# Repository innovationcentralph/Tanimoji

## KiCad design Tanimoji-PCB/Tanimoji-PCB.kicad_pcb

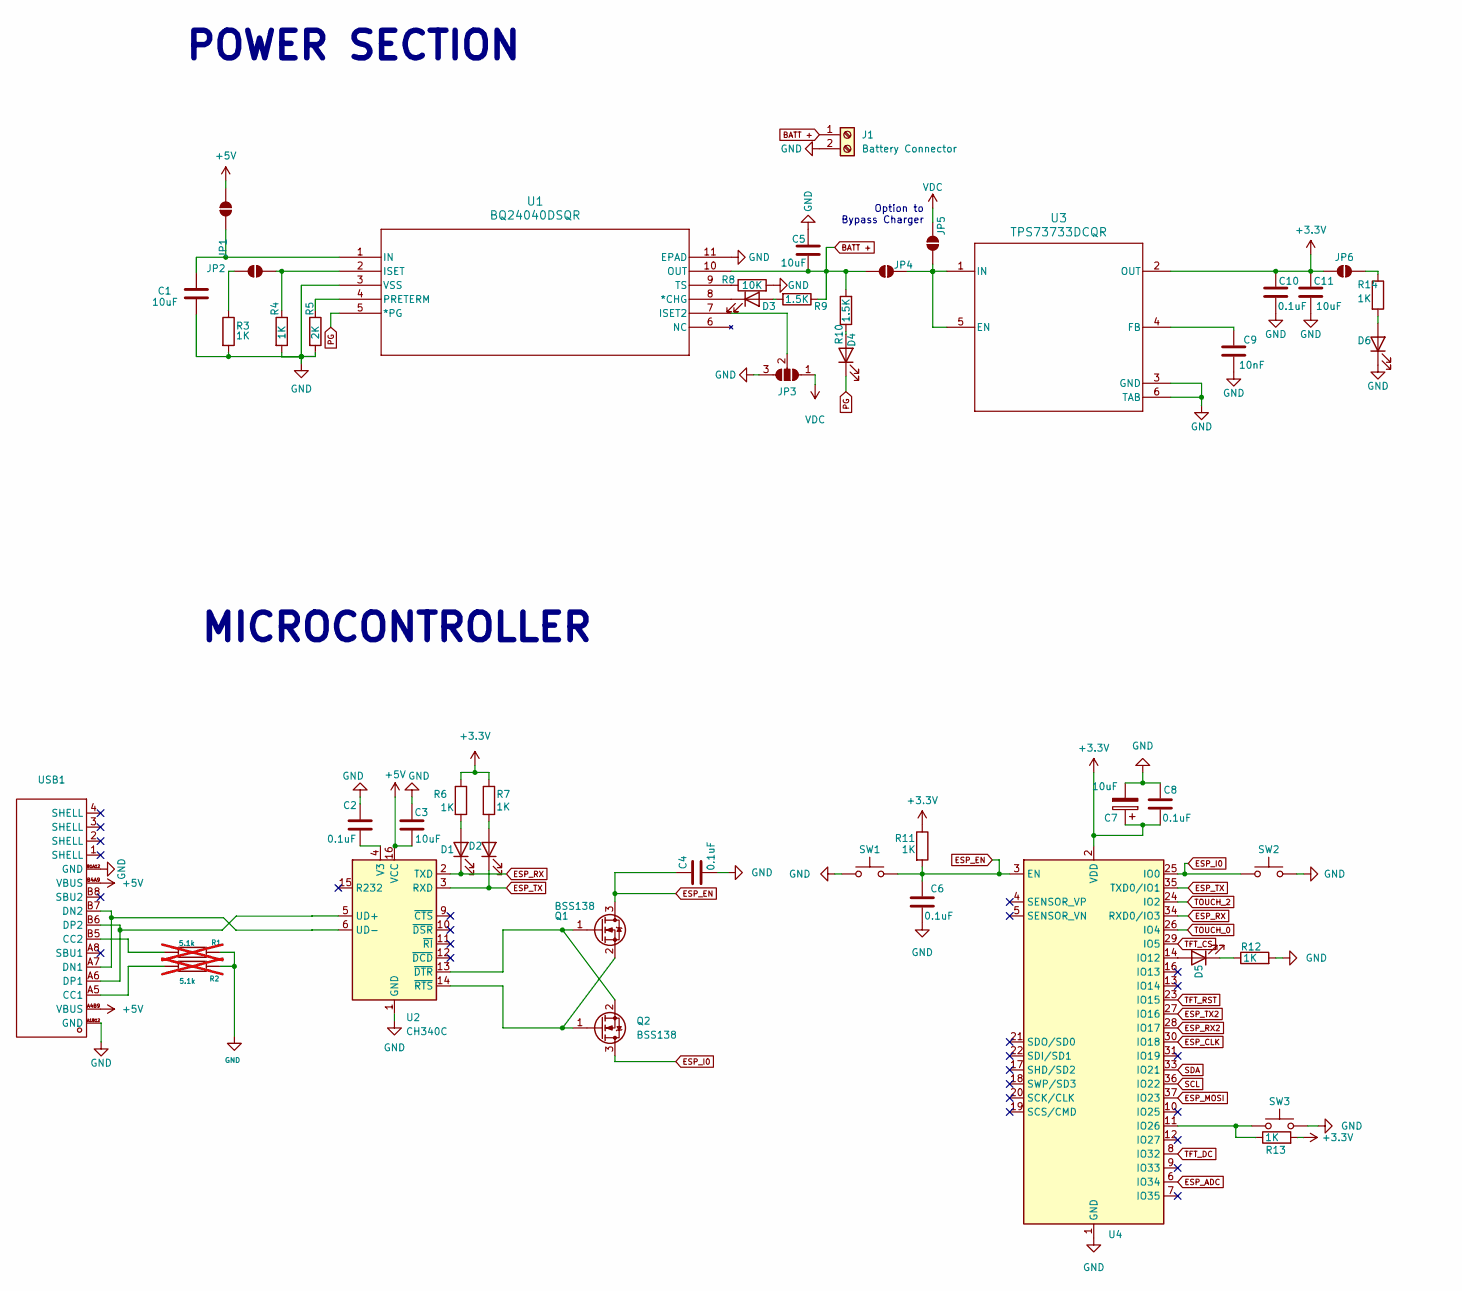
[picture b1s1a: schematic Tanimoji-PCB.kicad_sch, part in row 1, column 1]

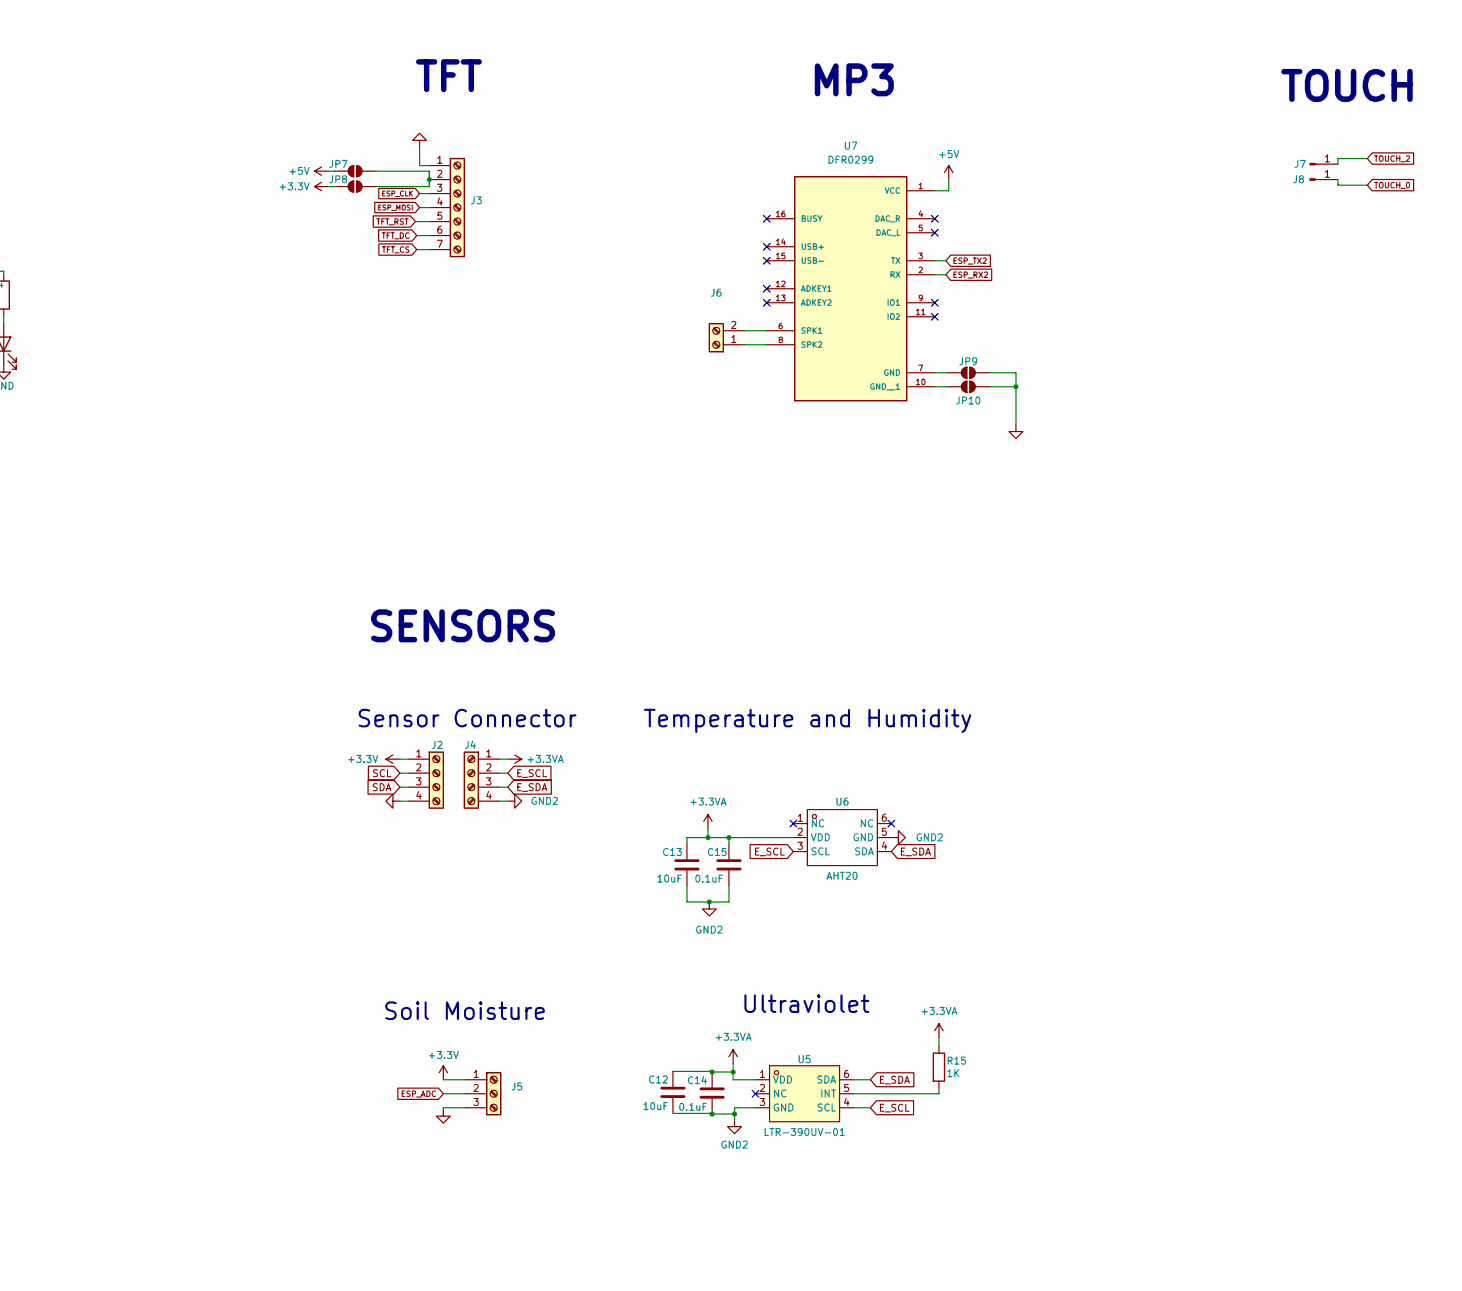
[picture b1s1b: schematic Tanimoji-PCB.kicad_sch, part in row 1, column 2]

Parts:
C1, C3, C5, C7, C11, C12, C13: 10uF; C_0805_2012Metric_Pad1.18x1.45mm_HandSolder; LCSC C15850
C2, C4, C6, C8, C10, C14, C15: 0.1uF; C_0805_2012Metric_Pad1.18x1.45mm_HandSolder; LCSC C49678
C9: 10nF; C_0402_1005Metric; LCSC C60133
D1, D2, D5, D6: LED; LED_0805_2012Metric_Pad1.15x1.40mm_HandSolder; LCSC C2297
D3: CHG; LED_0805_2012Metric_Pad1.15x1.40mm_HandSolder; LCSC C2286
D4: PGOOD; LED_0805_2012Metric_Pad1.15x1.40mm_HandSolder; LCSC C2297
J1: Battery Connector; JST_XH_B2B-XH-AM_1x02_P2.50mm_Vertical
J2, J4: Screw_Terminal_01x04; JST_XH_B4B-XH-AM_1x04_P2.50mm_Vertical
J3: Screw_Terminal_01x07; JST_XH_B7B-XH-AM_1x07_P2.50mm_Vertical
J5: Screw_Terminal_01x03; JST_XH_B3B-XH-AM_1x03_P2.50mm_Vertical
J6: Screw_Terminal_01x02; JST_XH_B2B-XH-AM_1x02_P2.50mm_Vertical
J7, J8: Conn_01x01_Pin; TestPoint_Loop_D2.54mm_Drill1.5mm_Beaded
JP1, JP2, JP4, JP5, JP6, JP7, JP8, JP9, JP10: SolderJumper_2_Open; SolderJumper-2_P1.3mm_Open_RoundedPad1.0x1.5mm
JP3: SolderJumper_3_Open; SolderJumper-3_P1.3mm_Open_RoundedPad1.0x1.5mm
Q1, Q2: BSS138; SOT-23; LCSC C426569
R1, R2: 5.1k; R_0603_1608Metric_Pad0.98x0.95mm_HandSolder; LCSC C103079; not fitted
R3, R4, R6, R7, R11, R12, R13, R14, R15: 1K; R_0603_1608Metric_Pad0.98x0.95mm_HandSolder; LCSC C21190
R5: 2K; R_0603_1608Metric_Pad0.98x0.95mm_HandSolder; LCSC C22975
R8: 10K; R_0603_1608Metric_Pad0.98x0.95mm_HandSolder; LCSC C25804
R9, R10: 1.5K; R_0603_1608Metric_Pad0.98x0.95mm_HandSolder; LCSC C22843
SW1, SW2: SW_Push; SW_Tactile_SPST_NO_Straight_CK_PTS636Sx25SMTRLFS; LCSC C2689642
SW3: SW_Push; SW_PUSH_6mm_H9.5mm; LCSC C2689642
U1: BQ24040DSQR; WSON-10_L2.0-W2.0-P0.40-BL-EP; LCSC C81080
U2: CH340C; SOP-16_3.9x9.9mm_P1.27mm; LCSC C84681
U3: TPS73733DCQR; SOT-223-6_L6.5-W3.5-P1.27-BL; LCSC C31334
U4: ESP32-WROOM-32; ESP32-WROOM-32U; LCSC C529577
U5: LTR-390UV-01; SENSOR-SMD_LTR-390UV-01; LCSC Part C492374
U6: AHT20; SENSOR-SMD_L3.0-W3.0-P1.00-BR; Manufacturer Part AHT20; LCSC Part Name AHT20
U7: DFR0299; MODULE_DFR0299
USB1: USB-C-SMD_TYPE-C16PIN; Manufacturer Part TYPE-C16PIN; LCSC Part Name Type-C 母 卧贴

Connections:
+3.3V: C7.1, C8.1, C10.2, C11.2, J2.1, J5.1, JP6.1 (A), JP8.1 (A), R6.1, R7.1, R11.1, R13.2, U3.2 (OUT), U4.2 (VDD)
+3.3VA: C12.1, C13.1, C14.2, C15.1, J4.1, R15.1, U5.1 (VDD), U6.2 (VDD)
+5V: C3.1, JP1.1 (A), JP7.1 (A), U2.16 (VCC), U7.1 (VCC), USB1.A4B9 (VBUS), USB1.B4A9 (VBUS)
BATT +: C5.2, J1.1, JP4.1 (A), R9.1, R10.2, U1.10 (OUT)
ESP_ADC: J5.2, U4.6 (IO34)
ESP_CLK: J3.3, U4.30 (IO18)
ESP_EN: C4.2, C6.2, Q1.3 (D), R11.2, SW1.2, U4.3 (EN)
ESP_I0: Q2.3 (D), SW2.1, U4.25 (IO0)
ESP_MOSI: J3.4, U4.37 (IO23)
ESP_RX: D1.1 (K), U2.2 (TXD), U4.34 (RXD0/IO3)
ESP_RX2: U4.28 (IO17), U7.2 (RX)
ESP_TX: D2.1 (K), U2.3 (RXD), U4.35 (TXD0/IO1)
ESP_TX2: U4.27 (IO16), U7.3 (TX)
E_SCL: J4.2, U5.4 (SCL), U6.3 (SCL)
E_SDA: J4.3, U5.6 (SDA), U6.4 (SDA)
GND: C1.2, C2.2, C3.2, C4.1, C5.1, C6.1, C7.2, C8.2, C9.1, C10.1, C11.1, D6.1 (K), J1.2, J2.4, J3.1, J5.3, JP3.3 (B), JP9.2 (B), JP10.2 (B), R1.2, R2.2, R3.2, R4.2, R5.2, R8.2, R12.2, SW1.1, SW2.2, SW3.2, U1.3 (VSS), U1.11 (EPAD), U2.1 (GND), U3.3 (GND), U3.6 (TAB), U4.1 (GND), U4.15 (GND), U4.38 (GND), U4.39 (GND), USB1.A1B12 (GND), USB1.B1A12 (GND)
GND2: C12.2, C13.2, C14.1, C15.2, J4.4, U5.3 (GND), U6.5 (GND)
unnamed: D1.2 (A), R6.2
unnamed: D2.2 (A), R7.2
unnamed: D3.2 (A), R9.2
unnamed: D3.1 (K), U1.8 (*CHG)
unnamed: D4.2 (A), R10.1
unnamed: D5.2 (A), U4.14 (IO12)
unnamed: D5.1 (K), R12.1
unnamed: D6.2 (A), R14.2
unnamed: J3.2, JP7.2 (B), JP8.2 (B)
unnamed: J6.1, U7.8 (SPK2)
unnamed: J6.2, U7.6 (SPK1)
unnamed: C1.1, JP1.2 (B), U1.1 (IN)
unnamed: JP2.1 (A), R4.1, U1.2 (ISET)
unnamed: JP2.2 (B), R3.1
unnamed: JP3.2 (C), U1.7 (ISET2)
unnamed: JP4.2 (B), JP5.2 (B), U3.1 (IN), U3.5 (EN)
unnamed: JP6.2 (B), R14.1
unnamed: JP9.1 (A), U7.7 (GND)
unnamed: JP10.1 (A), U7.10 (GND__1)
unnamed: Q1.1 (G), Q2.2 (S), U2.13 (~DTR)
unnamed: Q1.2 (S), Q2.1 (G), U2.14 (~RTS)
unnamed: R5.1, U1.4 (PRETERM)
unnamed: R8.1, U1.9 (TS)
unnamed: U2.5 (UD+), USB1.A6 (DP1), USB1.B6 (DP2)
unnamed: U2.6 (UD-), USB1.A7 (DN1), USB1.B7 (DN2)
unnamed: C2.1, U2.4 (V3)
unnamed: C9.2, U3.4 (FB)
unnamed: R13.1, SW3.1, U4.11 (IO26)
unnamed: R15.2, U5.5 (INT)
unnamed: R2.1, USB1.A5 (CC1)
unnamed: R1.1, USB1.B5 (CC2)
PG: D4.1 (K), U1.5 (*PG)
SCL: J2.2, U4.36 (IO22)
SDA: J2.3, U4.33 (IO21)
TFT_CS: J3.7, U4.29 (IO5)
TFT_DC: J3.6, U4.8 (IO32)
TFT_RST: J3.5, U4.23 (IO15)
TOUCH_0: J8.1, U4.26 (IO4)
TOUCH_2: J7.1, U4.24 (IO2)
VDC: JP3.1 (A), JP5.1 (A)

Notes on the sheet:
Temperature and Humidity
TOUCH
SENSORS
MICROCONTROLLER
MP3
Sensor Connector
Soil Moisture
TFT
POWER SECTION
Option to Bypass Charger
Ultraviolet

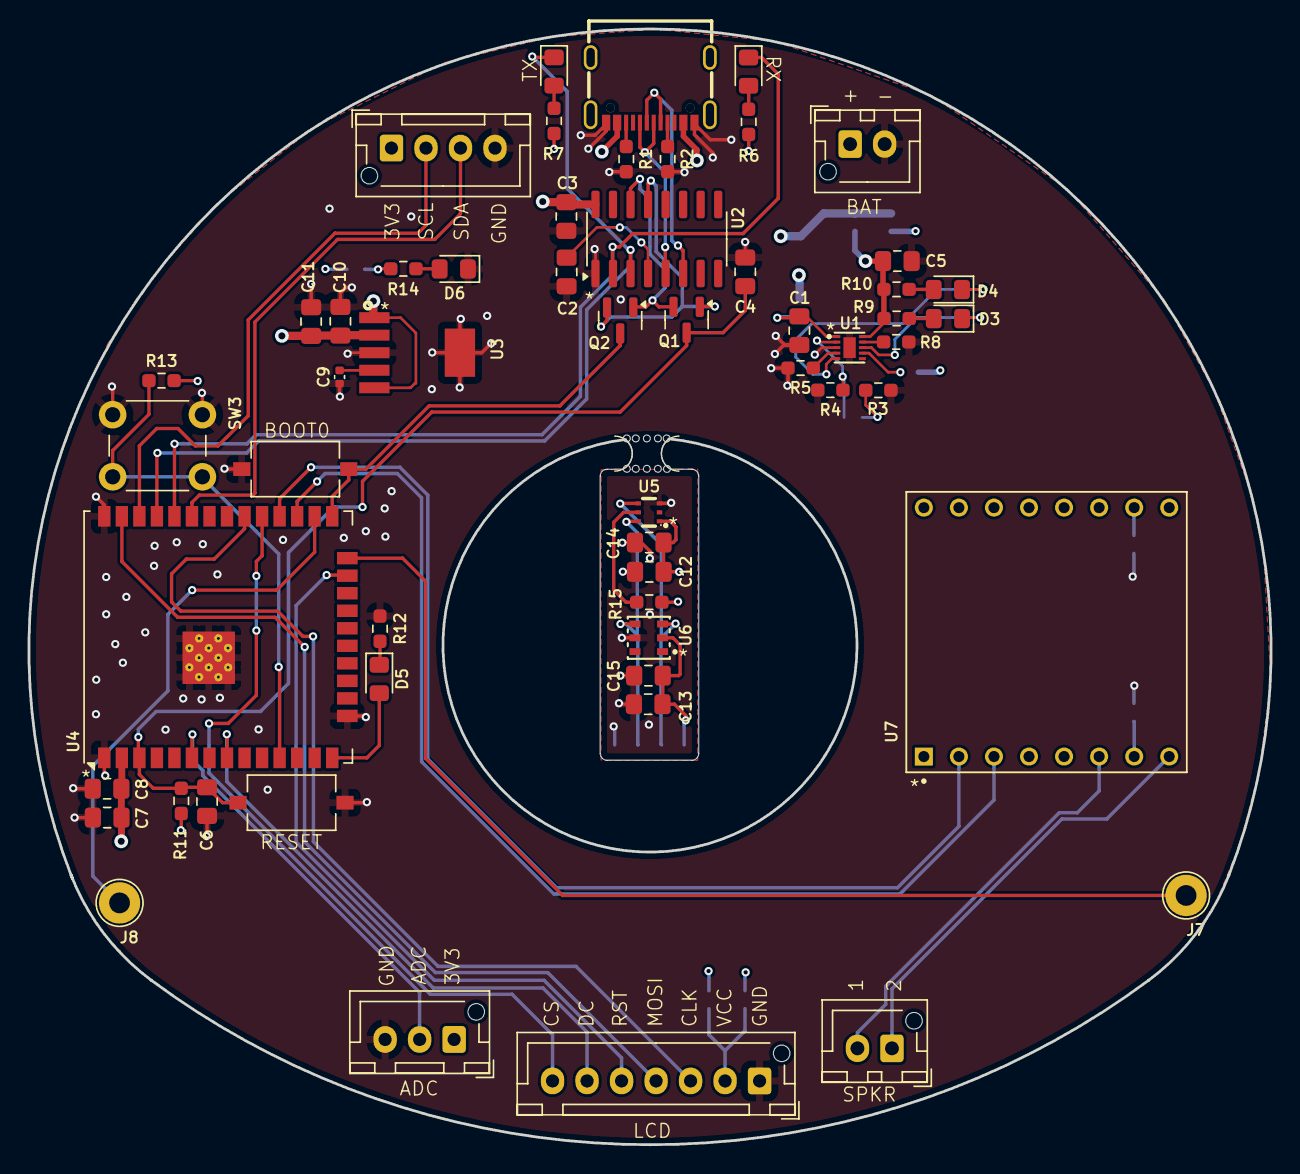
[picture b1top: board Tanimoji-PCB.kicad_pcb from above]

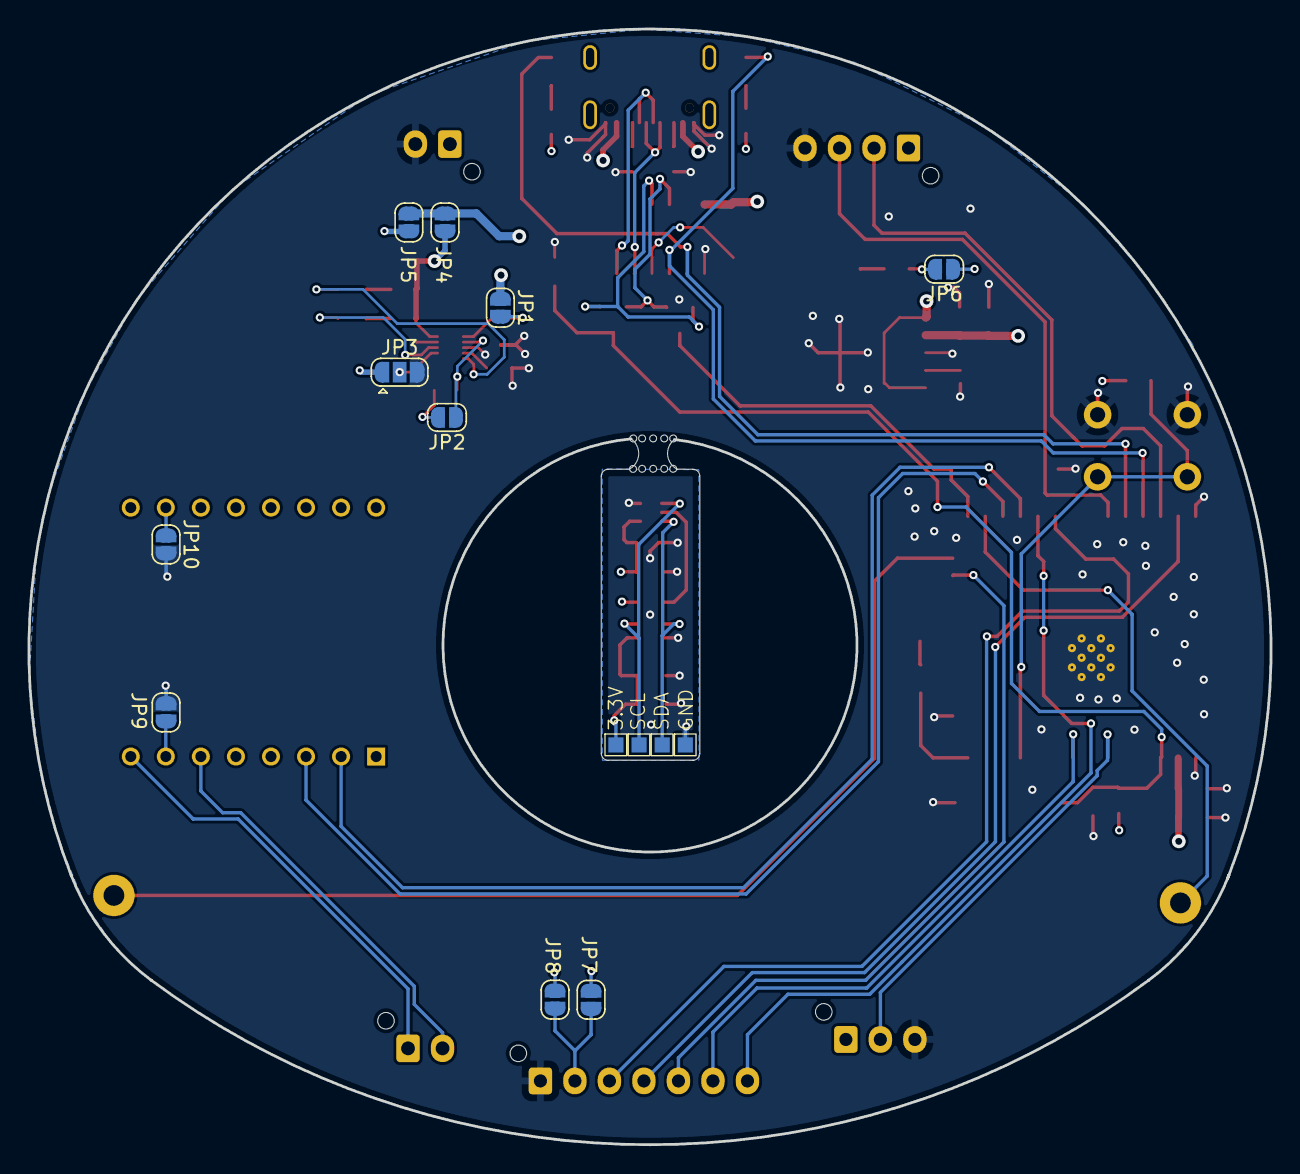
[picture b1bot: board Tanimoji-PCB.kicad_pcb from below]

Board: 4 copper layers, 90.0 x 80.8 mm, 67 parts (10 on the bottom side), 57 nets.

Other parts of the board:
mouse-bite-2.54mm-slot: VAL**; mouse-bite-2.54mm-slot

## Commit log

2025-09-18 Initial Commit Schematic Done
2025-09-18 updated pcb
